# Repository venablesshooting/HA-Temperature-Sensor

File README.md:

# HA-Temperature-Sensor
Battery powered temperature and humidity sensor

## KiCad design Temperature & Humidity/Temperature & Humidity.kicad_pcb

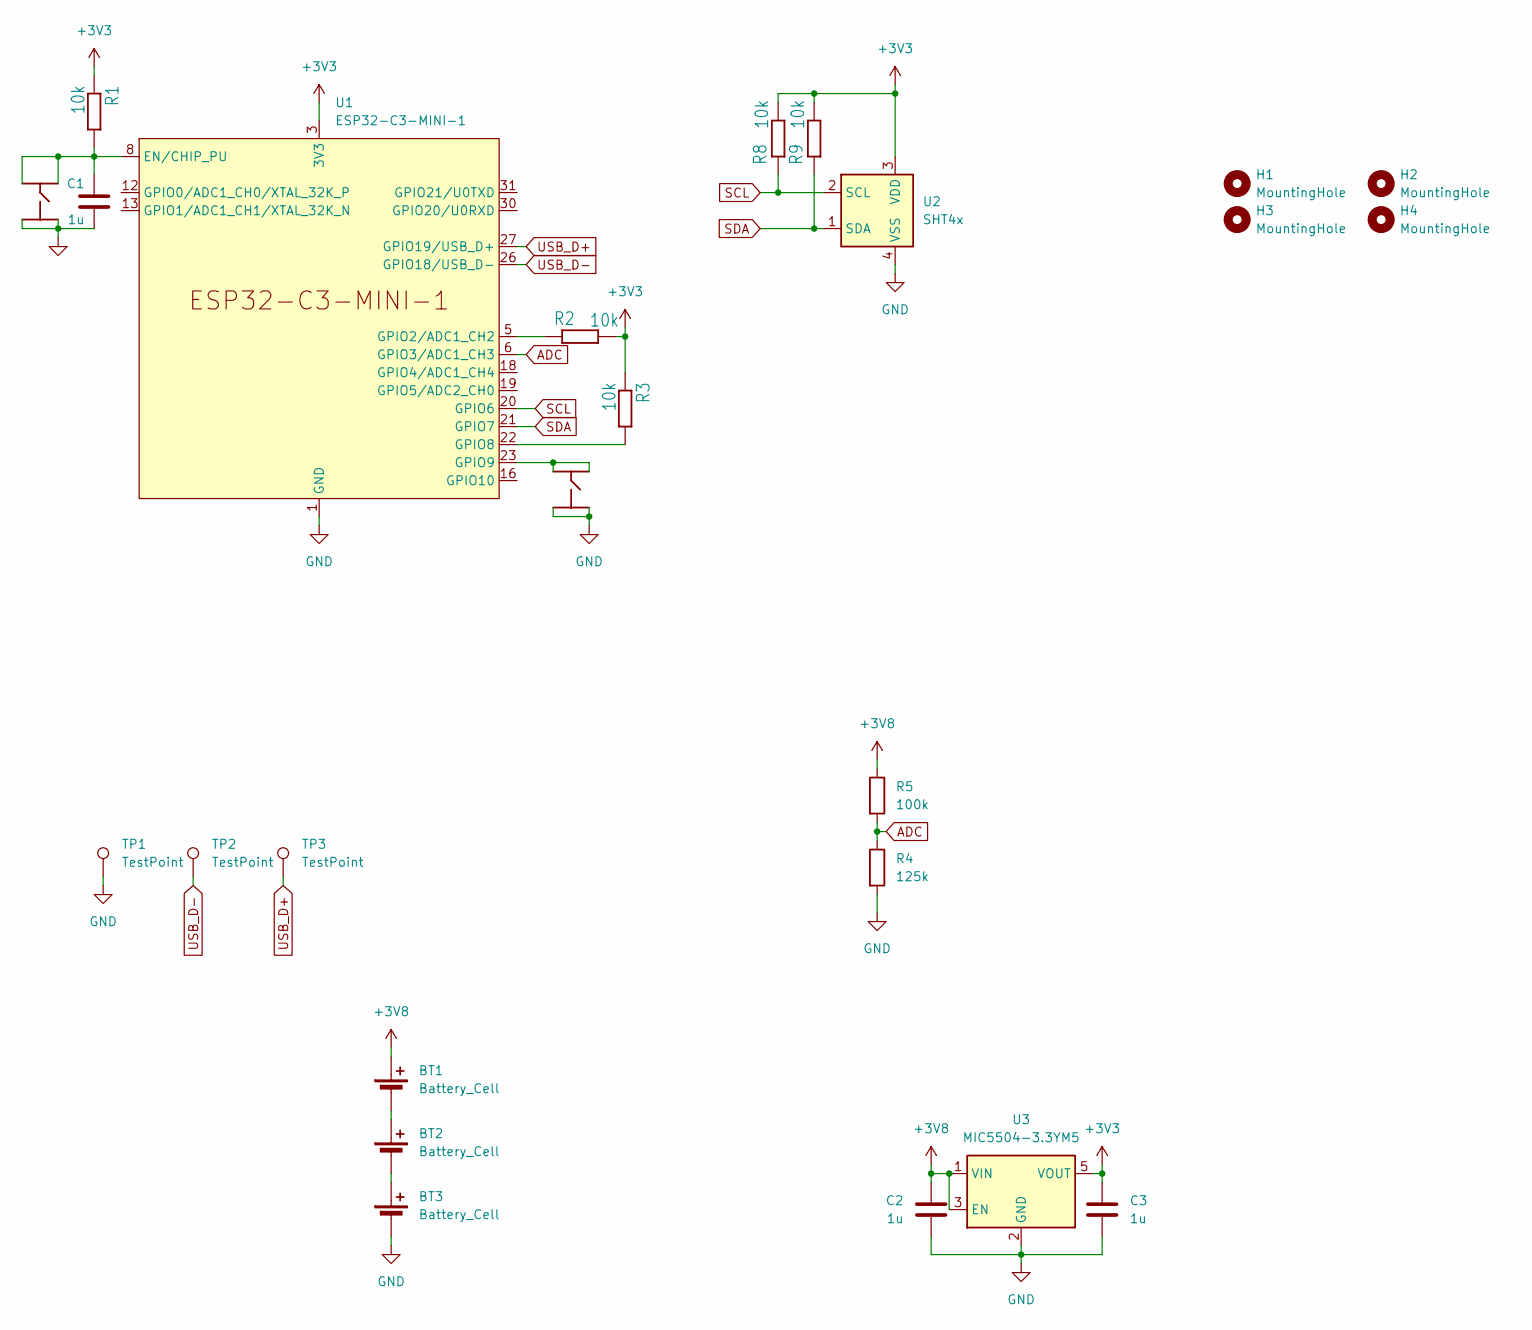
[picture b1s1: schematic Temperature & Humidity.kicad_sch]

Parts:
BT1, BT2, BT3: Battery_Cell; Keystone 92
C1, C2, C3: 1u; C_0603_1608Metric
H1, H2, H3, H4: MountingHole; MountingHole_3.2mm_M3_DIN965_Pad
R1, R2, R3, R8, R9: 10k; R_0603_1608Metric
R4: 125k; R_0603_1608Metric
R5: 100k; R_0603_1608Metric
TP1, TP2, TP3: TestPoint; TestPoint_Pad_D1.5mm
U1: ESP32-C3-MINI-1
U2: SHT4x; Sensirion_DFN-4_1.5x1.5mm_P0.8mm_SHT4x_NoCentralPad
U3: MIC5504-3.3YM5; SOT-23-5
s1, s3: TS-1070A; TS-1070A-B3D2

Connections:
+3V3: C3.1, R1.1, R2.2, R3.1, R8.2, R9.2, U1.3 (3V3), U2.3 (VDD), U3.5 (VOUT)
+3V8: BT1.1 (+), C2.1, R5.1, U3.1 (VIN), U3.3 (EN)
ADC: R4.1, R5.2, U1.6 (GPIO3/ADC1_CH3)
GND: BT3.2 (-), C1.2, C2.2, C3.2, R4.2, TP1.1, U1.1 (GND), U1.2 (GND), U1.11 (GND), U1.14 (GND), U1.36 (GND), U1.37 (GND), U1.38 (GND), U1.39 (GND), U1.40 (GND), U1.41 (GND), U1.42 (GND), U1.43 (GND), U1.44 (GND), U1.45 (GND), U1.46 (GND), U1.47 (GND), U1.48 (GND), U1.49 (GND), U1.50 (GND), U1.51 (GND), U1.52 (GND), U1.53 (GND), U2.4 (VSS), U3.2 (GND), s1.P3 (3), s1.P4 (4), s3.P3 (3), s3.P4 (4)
unnamed: BT1.2 (-), BT2.1 (+)
unnamed: BT2.2 (-), BT3.1 (+)
unnamed: C1.1, R1.2, U1.8 (EN/CHIP_PU), s1.P1 (1), s1.P2 (2)
unnamed: R2.1, U1.5 (GPIO2/ADC1_CH2)
unnamed: R3.2, U1.22 (GPIO8)
unnamed: U1.23 (GPIO9), s3.P1 (1), s3.P2 (2)
SCL: R8.1, U1.20 (GPIO6), U2.2 (SCL)
SDA: R9.1, U1.21 (GPIO7), U2.1 (SDA)
USB_D+: TP3.1, U1.27 (GPIO19/USB_D+)
USB_D-: TP2.1, U1.26 (GPIO18/USB_D-)

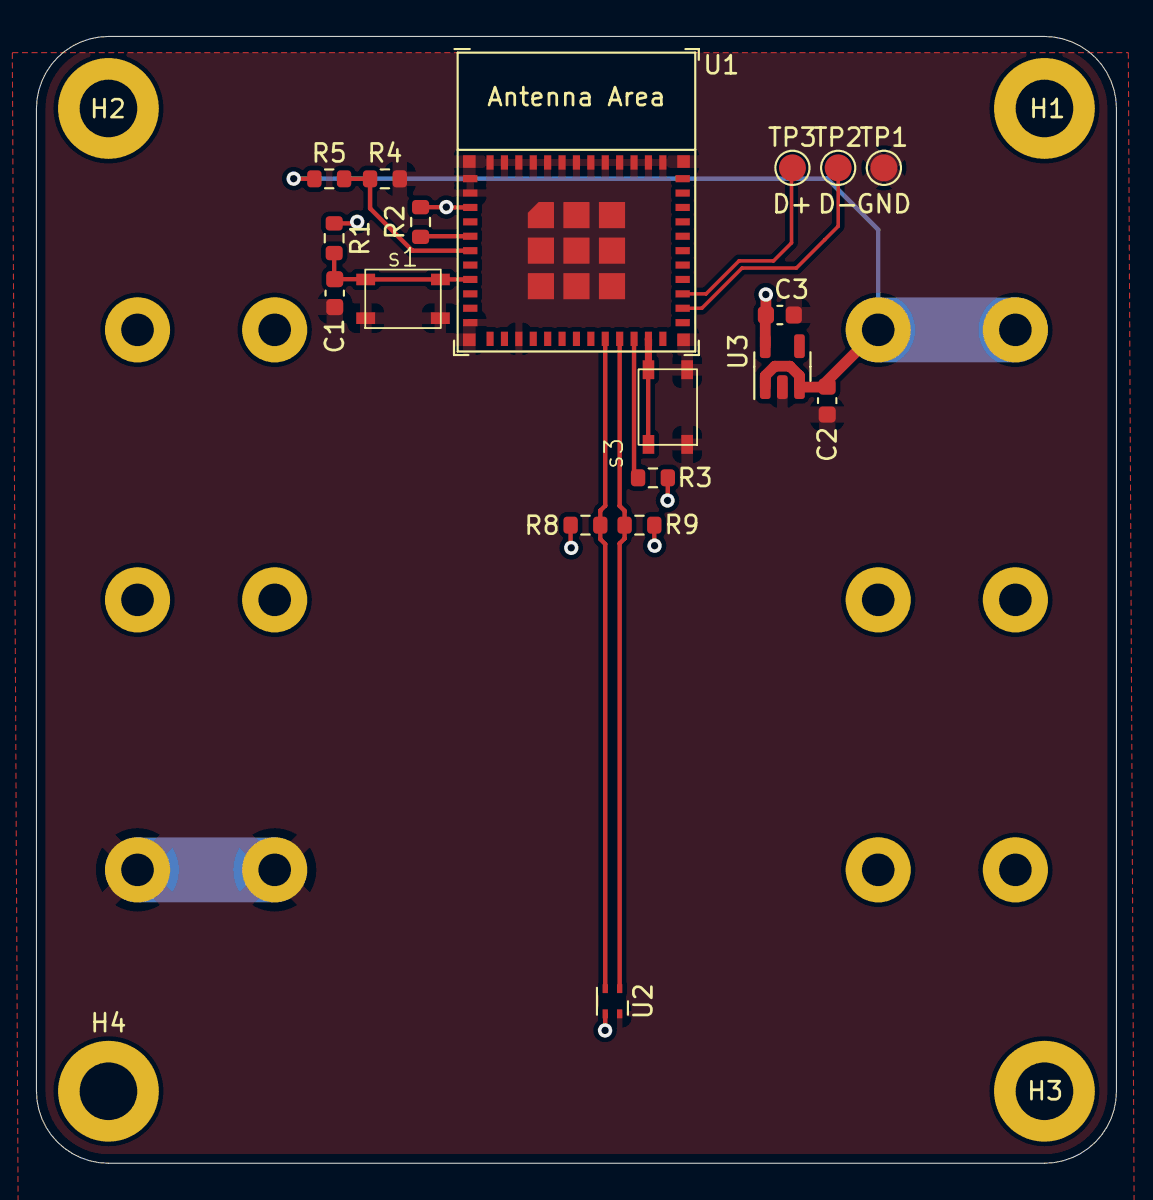
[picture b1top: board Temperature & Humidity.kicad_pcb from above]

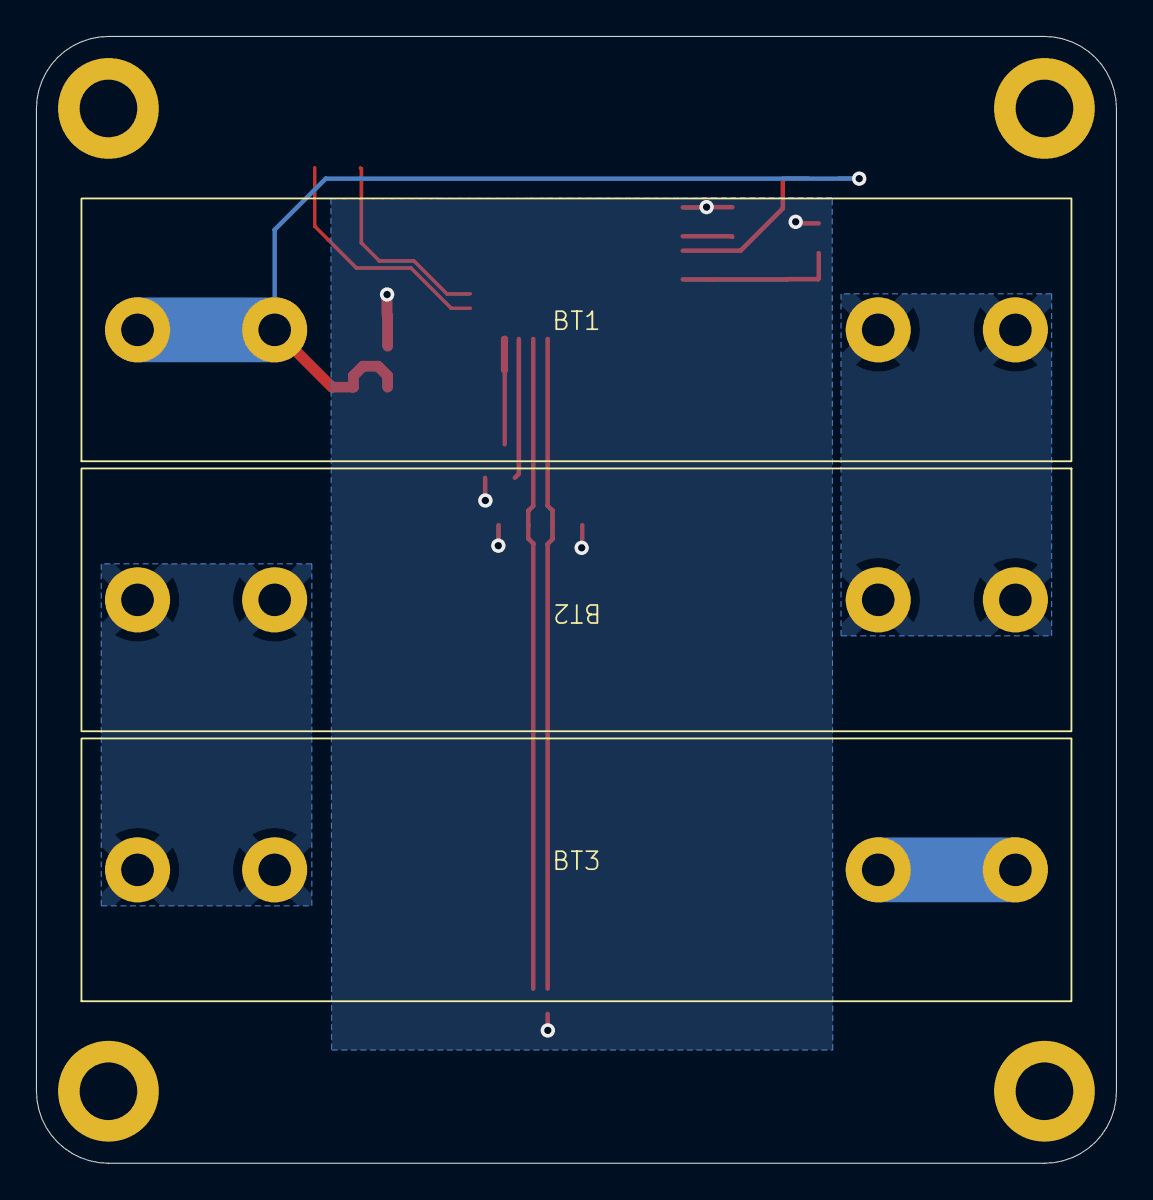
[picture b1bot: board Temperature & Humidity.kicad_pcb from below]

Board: 2 copper layers, 60.0 x 62.6 mm, 25 parts (3 on the bottom side), 14 nets.

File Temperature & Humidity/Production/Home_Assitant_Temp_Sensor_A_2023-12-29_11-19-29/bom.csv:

Designator,Footprint,Quantity,Value,LCSC Part #
"BT1, BT2, BT3",Keystone 92,3,Battery_Cell,
"C1, C2, C3",0603,3,1u,
"H1, H2, H3, H4",MountingHole_3.2mm_M3_DIN965_Pad,4,MountingHole,
"R1, R2, R3, R8, R9",0603,5,10k,
"TP1, TP2, TP3",TestPoint_Pad_D1.5mm,3,TestPoint,
U1,ESP32-C3-MINI-1,1,ESP32-C3-MINI-1,
U2,Sensirion_DFN-4_1.5x1.5mm_P0.8mm_SHT4x_NoCentralPad,1,SHT4x,
U3,SOT-23-5,1,MIC5504-3.3YM5,
"s1, s3",TS-1070A-B3D2,2,TS-1070A,

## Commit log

2023-12-31 added battery level sensor
